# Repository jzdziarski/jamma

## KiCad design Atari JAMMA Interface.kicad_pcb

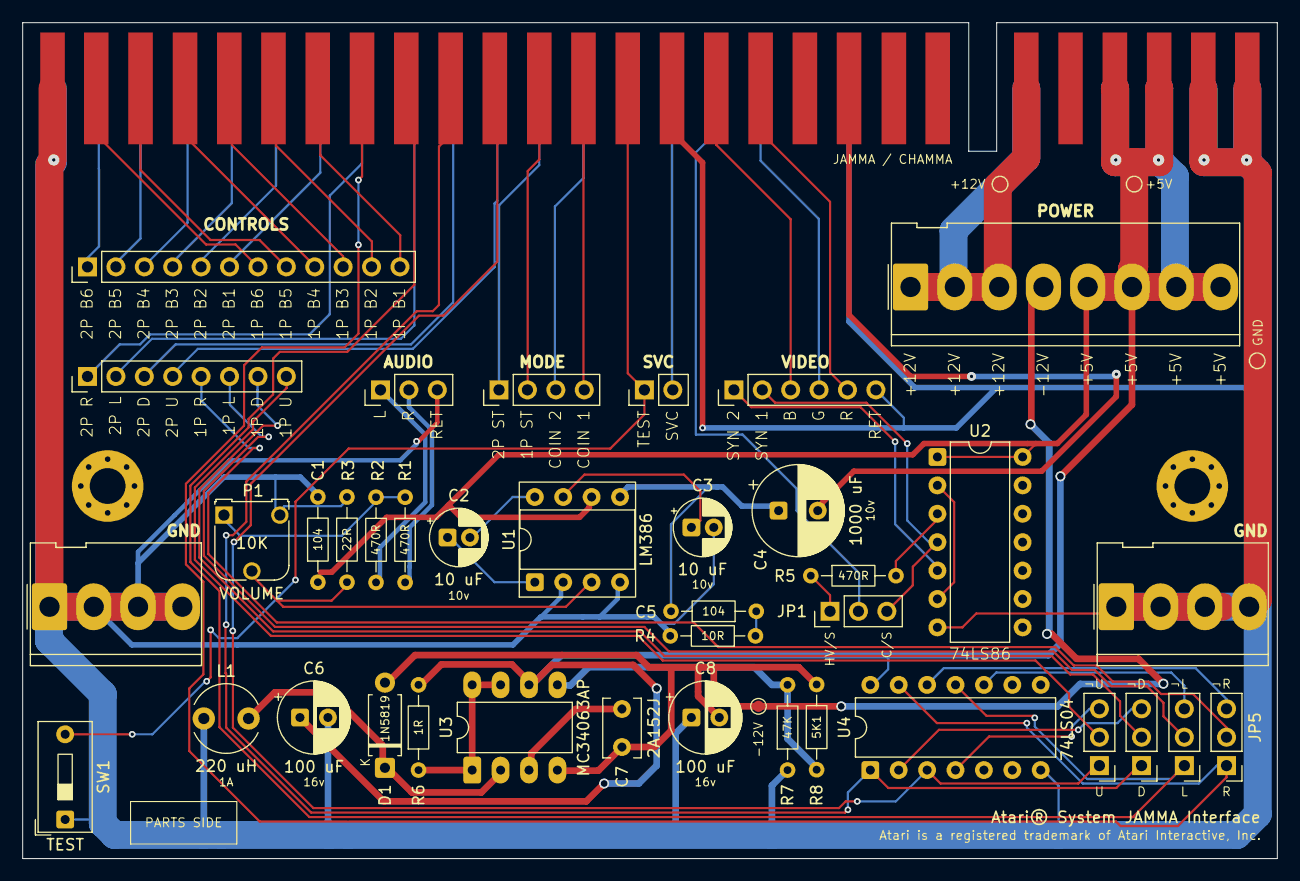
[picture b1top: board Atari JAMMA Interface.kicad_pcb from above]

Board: 2 copper layers, 112.2 x 74.8 mm, 43 parts (0 on the bottom side), 61 nets.

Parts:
+5V, +12V: TestPoint_Pad_D1.0mm
-12V: TestPoint_Pad_D1.0mm
AUDIO: PinHeader_1x03_P2.54mm_Vertical
C1, C5: 104; R_Axial_DIN0204_L3.6mm_D1.6mm_P7.62mm_Horizontal
C2, C3: 10 uF; CP_Radial_D5.0mm_P2.00mm
C4: 1000 uF; CP_Radial_D8.0mm_P3.50mm
C6, C8: 100 uF; CP_Radial_D6.3mm_P2.50mm
C7: 2A152J; C_Disc_D5.1mm_W3.2mm_P3.4mm
CONTROLS: PinHeader_1x12_P2.54mm_Vertical
D1: 1N5819; D_A-405_P7.62mm_Horizontal
DIRECTIONALS: PinHeader_1x08_P2.54mm_Vertical
GND: TestPoint_Pad_D1.0mm
GND#2, GND#3: Molex_KK-396_5273-04A_1x04_P3.96mm_Vertical
HV/S: PinHeader_1x03_P2.54mm_Vertical
HV/S#2, HV/S#3, HV/S#4, HV/S#5: PinHeader_1x03_P2.54mm_Vertical
JAMMA / CHAMMA: HDR_JAMMA_56P_EDGE_CONNECTOR
L1: 220 uH; L_Radial_D6.0mm_P4.00mm
MODE: PinHeader_1x04_P2.54mm_Vertical
P1: 10K; Potentiometer_Runtron_RM-065_Vertical
POWER: Molex_KK-396_5273-08A_1x08_P3.96mm_Vertical
R1, R2, R5: 470R; R_Axial_DIN0204_L3.6mm_D1.6mm_P7.62mm_Horizontal
R3: 22R; R_Axial_DIN0204_L3.6mm_D1.6mm_P7.62mm_Horizontal
R4: 10R; R_Axial_DIN0204_L3.6mm_D1.6mm_P7.62mm_Horizontal
R6: 1R; R_Axial_DIN0204_L3.6mm_D1.6mm_P7.62mm_Horizontal
R7: 47K; R_Axial_DIN0204_L3.6mm_D1.6mm_P7.62mm_Horizontal
R8: 5K1; R_Axial_DIN0204_L3.6mm_D1.6mm_P7.62mm_Horizontal
SVC: PinHeader_1x02_P2.54mm_Vertical
TEST: SW1; SW_DIP_SPSTx01_Slide_9.78x4.72mm_W7.62mm_P2.54mm
U1: LM386; DIP-8_W7.62mm_Socket
U2: DIP-14_W7.62mm
U3: MC34063AP; DIP-8_W7.62mm_LongPads
U4: 74LS04; DIP-14_W7.62mm
VIDEO: PinHeader_1x06_P2.54mm_Vertical

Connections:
1P_!D: HV/S#5.3, U4.2
1P_!L: HV/S.3, U4.10
1P_!R: HV/S#2.3, U4.12
1P_!U: HV/S#3.3, U4.4
1P_B1: CONTROLS.12, JAMMA / CHAMMA.22
1P_B2: CONTROLS.11, JAMMA / CHAMMA.23
1P_B3: CONTROLS.10, JAMMA / CHAMMA.24
1P_B4: CONTROLS.9, JAMMA / CHAMMA.25
1P_B5: CONTROLS.8, JAMMA / CHAMMA.26
1P_B6: CONTROLS.7, JAMMA / CHAMMA.27
1P_D: HV/S#5.1, JAMMA / CHAMMA.19, U4.1
1P_D_OUT: DIRECTIONALS.7, HV/S#5.2
1P_L: HV/S.1, JAMMA / CHAMMA.20, U4.11
1P_L_OUT: DIRECTIONALS.6, HV/S.2
1P_R: HV/S#2.1, JAMMA / CHAMMA.21, U4.13
1P_R_OUT: DIRECTIONALS.5, HV/S#2.2
1P_START: JAMMA / CHAMMA.17, MODE.2
1P_U: HV/S#3.1, JAMMA / CHAMMA.18, U4.3
1P_U_OUT: DIRECTIONALS.8, HV/S#3.2
2P_B1: CONTROLS.6, JAMMA / CHAMMA.Z
2P_B2: CONTROLS.5, JAMMA / CHAMMA.a
2P_B3: CONTROLS.4, JAMMA / CHAMMA.b
2P_B4: CONTROLS.3, JAMMA / CHAMMA.c
2P_B5: CONTROLS.2, JAMMA / CHAMMA.d
2P_B6: CONTROLS.1, JAMMA / CHAMMA.e
2P_D: DIRECTIONALS.3, JAMMA / CHAMMA.W
2P_L: DIRECTIONALS.2, JAMMA / CHAMMA.X
2P_R: DIRECTIONALS.1, JAMMA / CHAMMA.Y
2P_START: JAMMA / CHAMMA.U, MODE.1
2P_U: DIRECTIONALS.4, JAMMA / CHAMMA.V
+5V: +5V.1, C1.1, C6.1, JAMMA / CHAMMA.3, JAMMA / CHAMMA.4, JAMMA / CHAMMA.C, JAMMA / CHAMMA.D, POWER.5, POWER.6, POWER.7, POWER.8, R6.2, U1.6, U2.1, U2.14, U3.6, U4.14
+12V: +12V.1, JAMMA / CHAMMA.6, JAMMA / CHAMMA.F, POWER.1, POWER.2, POWER.3
-12V: -12V.1, C7.1, C8.2, D1.2, POWER.4, R8.2, U3.4
AUDIO_L: AUDIO.1, R2.2
AUDIO_MONO: P1.1, R1.1, R2.1
AUDIO_R: AUDIO.2, R1.2
C5_R4: C5.1, R4.1
CINV_R10_R9: R7.2, R8.1, U3.5
COIN_1: JAMMA / CHAMMA.16, MODE.4
COIN_2: JAMMA / CHAMMA.T, MODE.3
GND: AUDIO.3, C1.2, C3.2, C6.2, C8.1, GND.1, GND#2.1, GND#2.2, GND#2.3, GND#2.4, GND#3.1, GND#3.2, GND#3.3, GND#3.4, JAMMA / CHAMMA.1, JAMMA / CHAMMA.2, JAMMA / CHAMMA.14, JAMMA / CHAMMA.28, JAMMA / CHAMMA.A, JAMMA / CHAMMA.B, JAMMA / CHAMMA.L, JAMMA / CHAMMA.f, L1.1, P1.3, R3.2, R4.2, R7.1, TEST.1, U1.2, U1.4, U2.7, U4.7, VIDEO.6
PREAMP: P1.2, R3.1, U1.3
PREAMP_OUT: C4.1, C5.2, U1.5
R8: R6.1, U3.1, U3.7, U3.8
SERVICE: JAMMA / CHAMMA.R, SVC.2
SPKR+: C4.2, JAMMA / CHAMMA.10
SWE: D1.1, L1.2, U3.2
TEST: JAMMA / CHAMMA.15, SVC.1, TEST.2
U3_CAP: C7.2, U3.3
U4_BYPASS: C3.1, U1.7
U4_GAIN_P1: C2.1, U1.1
U4_GAIN_P8: C2.2, U1.8
VID_B: JAMMA / CHAMMA.13, VIDEO.3
VID_CSYNC: HV/S#4.2, JAMMA / CHAMMA.P
VID_G: JAMMA / CHAMMA.N, VIDEO.4
VID_NXOR: HV/S#4.1, R5.1
VID_NXOR_R5: R5.2, U2.3
VID_R: JAMMA / CHAMMA.12, VIDEO.5
VID_SYN1: HV/S#4.3, U2.4, VIDEO.2
VID_SYN2: U2.5, VIDEO.1
VID_XOR: U2.2, U2.6

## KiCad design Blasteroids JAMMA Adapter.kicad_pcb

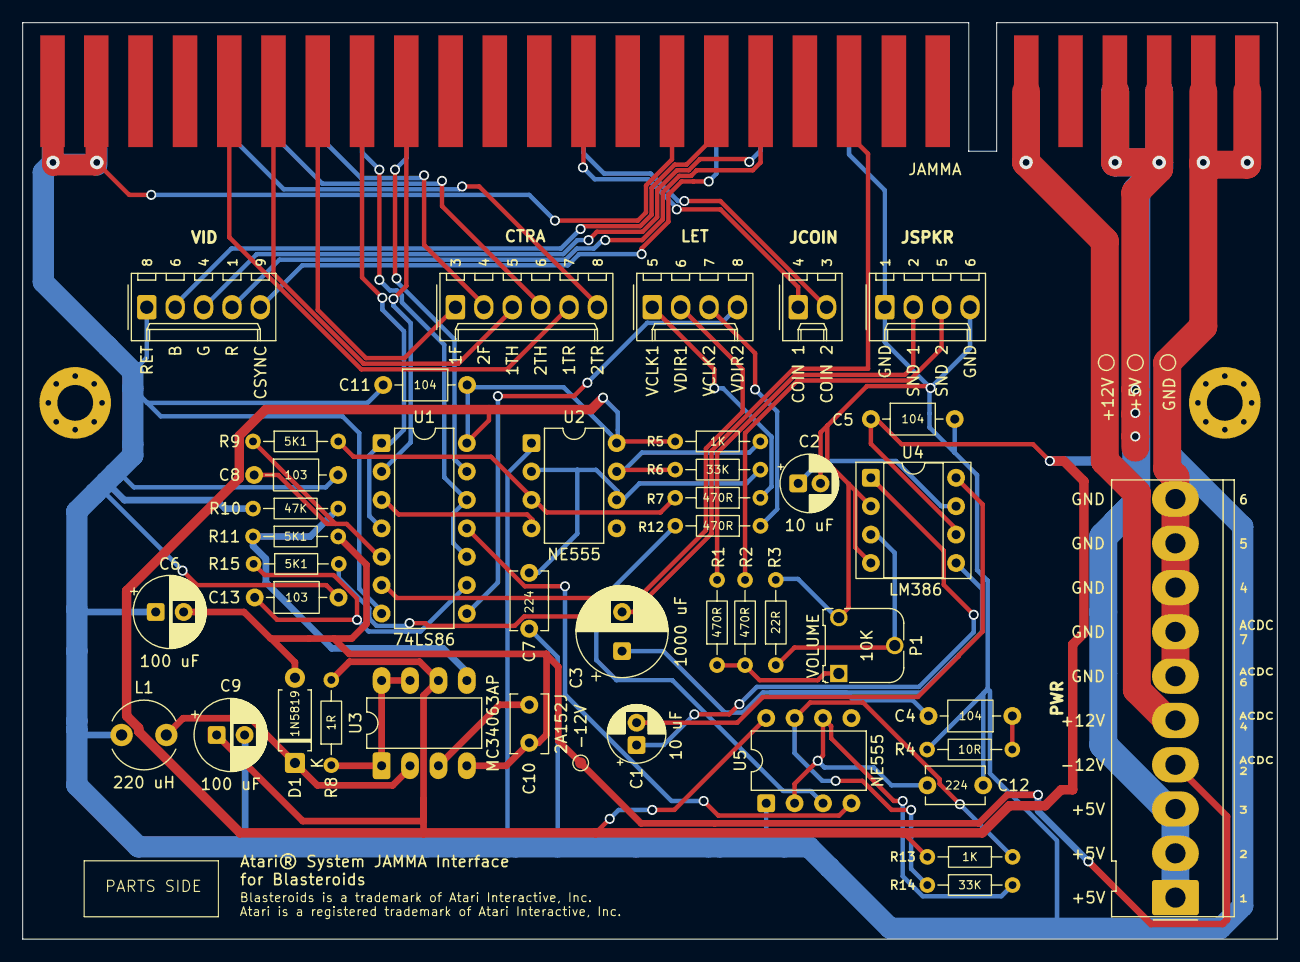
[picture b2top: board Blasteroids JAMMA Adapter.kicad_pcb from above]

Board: 2 copper layers, 112.2 x 82.0 mm, 49 parts (0 on the bottom side), 48 nets.

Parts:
+5V: TP2; TestPoint_Pad_D1.0mm
+12V: TP3; TestPoint_Pad_D1.0mm
-12V: TP4; TestPoint_Pad_D1.0mm
C1, C2: 10 uF; CP_Radial_D5.0mm_P2.00mm
C3: 1000 uF; CP_Radial_D8.0mm_P3.50mm
C4, C5, C11: 104; C_Axial_L3.8mm_D2.6mm_P7.50mm_Horizontal
C6, C9: 100 uF; CP_Radial_D6.3mm_P2.50mm
C7, C12: 224; C_Disc_D5.1mm_W3.2mm_P5.00mm
C8, C13: 103; C_Axial_L3.8mm_D2.6mm_P7.50mm_Horizontal
C10: 2A152J; C_Disc_D5.1mm_W3.2mm_P3.4mm
CTRA: Molex_KK-254_AE-6410-06A_1x06_P2.54mm_Vertical
D1: 1N5819; D_A-405_P7.62mm_Horizontal
GND: TP1; TestPoint_Pad_D1.0mm
JAMMA: HDR_JAMMA_56P_EDGE_CONNECTOR
JCOIN: Molex_KK-254_AE-6410-02A_1x02_P2.54mm_Vertical
JSPKR: Molex_KK-254_AE-6410-04A_1x04_P2.54mm_Vertical
L1: 220 uH; L_Radial_D6.0mm_P4.00mm
LET: Molex_KK-254_AE-6410-04A_1x04_P2.54mm_Vertical
P1: 10K; Potentiometer_Runtron_RM-065_Vertical
PMH1, PMH4: MountingHole_3.2mm_M3_Pad_Via
PWR: Molex_KK-396_5273-10A_1x10_P3.96mm_Vertical
R1: R1; R_Axial_DIN0204_L3.6mm_D1.6mm_P7.62mm_Horizontal
R2, R7, R12: 470R; R_Axial_DIN0204_L3.6mm_D1.6mm_P7.62mm_Horizontal
R3: 22R; R_Axial_DIN0204_L3.6mm_D1.6mm_P7.62mm_Horizontal
R4: R_Axial_DIN0204_L3.6mm_D1.6mm_P7.62mm_Horizontal
R5, R13: 1K; R_Axial_DIN0204_L3.6mm_D1.6mm_P7.62mm_Horizontal
R6, R14: 33K; R_Axial_DIN0204_L3.6mm_D1.6mm_P7.62mm_Horizontal
R8: 1R; R_Axial_DIN0204_L3.6mm_D1.6mm_P7.62mm_Horizontal
R9, R11, R15: 5K1; R_Axial_DIN0204_L3.6mm_D1.6mm_P7.62mm_Horizontal
R10: 47K; R_Axial_DIN0204_L3.6mm_D1.6mm_P7.62mm_Horizontal
U1: 74LS86; DIP-14_W7.62mm
U2, U5: NE555; DIP-8_W7.62mm
U3: MC34063AP; DIP-8_W7.62mm_LongPads
U4: LM386; DIP-8_W7.62mm_Socket
VID: Molex_KK-254_AE-6410-05A_1x05_P2.54mm_Vertical

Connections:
1P_B1: CTRA.1, JAMMA.22
1P_B2: CTRA.3, JAMMA.23
1P_B3: CTRA.5, JAMMA.24
1P_L: JAMMA.20, U1.2
1P_R: JAMMA.21, U1.1, U1.4
2P_B1: CTRA.2, JAMMA.Z
2P_B2: CTRA.4, JAMMA.a
2P_B3: CTRA.6, JAMMA.b
2P_L: JAMMA.X, U1.13
2P_R: JAMMA.Y, U1.10, U1.12
+5V: +5V.1, C5.1, C9.1, C11.2, JAMMA.3, JAMMA.4, JAMMA.C, JAMMA.D, PWR.1, PWR.2, PWR.3, R5.1, R8.2, R13.1, U1.14, U2.8, U3.6, U4.6, U5.8
+12V: +12V.1, JAMMA.6, JAMMA.F, PWR.5
-12V: -12V.1, C6.2, C10.1, D1.2, PWR.4, R11.2, U3.4
AUDIO_L: JSPKR.3, R2.2
AUDIO_MONO: P1.1, R1.1, R2.1
AUDIO_OUT: C3.2, JAMMA.10
AUDIO_PREAMP: P1.2, R3.1, U4.3
AUDIO_PREAMP_OUT: C3.1, C4.2, U4.5
AUDIO_R: JSPKR.2, R1.2
C4_R4: C4.1, R4.1
CINV_R10_R9: R10.2, R11.1, U3.5
COIN_1: JAMMA.16, JCOIN.1
COIN_2: JAMMA.T, JCOIN.2
GND: C2.2, C5.2, C6.1, C7.1, C8.2, C9.2, C11.1, C12.1, C13.2, GND.1, JAMMA.1, JAMMA.2, JAMMA.14, JAMMA.27, JAMMA.28, JAMMA.A, JAMMA.B, JAMMA.L, JAMMA.e, JAMMA.f, JSPKR.1, JSPKR.4, L1.1, P1.3, PWR.6, PWR.7, PWR.8, PWR.9, PWR.10, R3.2, R4.2, R10.1, U1.7, U2.1, U4.2, U4.4, U5.1, VID.1
R8: R8.1, U3.1, U3.7, U3.8
SWE: D1.1, L1.2, U3.2
U2_DIS: R5.2, R6.1, U2.7
U2_RESET: U1.3, U2.4
U2_THR: C7.2, R6.2, U2.2, U2.6
U3_CAP: C10.2, U3.3
U4_BYPASS: C2.1, U4.7
U4_GAIN_P1: C1.1, U4.1
U4_GAIN_P8: C1.2, U4.8
U5_DIS: R13.2, R14.1, U5.7
U5_RESET: U1.11, U5.4
U5_THR: C12.2, R14.2, U5.2, U5.6
VCLK1: R7.2, R9.2, U2.3
VCLK1_DELAYED: C8.1, R9.1, U1.5
VCLK1_OUT: LET.1, R7.1
VCLK2: R12.2, R15.2, U5.3
VCLK2_DELAYED: C13.1, R15.1, U1.9
VCLK2_OUT: LET.3, R12.1
VDIR1_OUT: LET.2, U1.6
VDIR2_OUT: LET.4, U1.8
VIDEO_B: JAMMA.13, VID.2
VIDEO_G: JAMMA.N, VID.3
VIDEO_R: JAMMA.12, VID.4
VIDEO_SYNC: JAMMA.P, VID.5

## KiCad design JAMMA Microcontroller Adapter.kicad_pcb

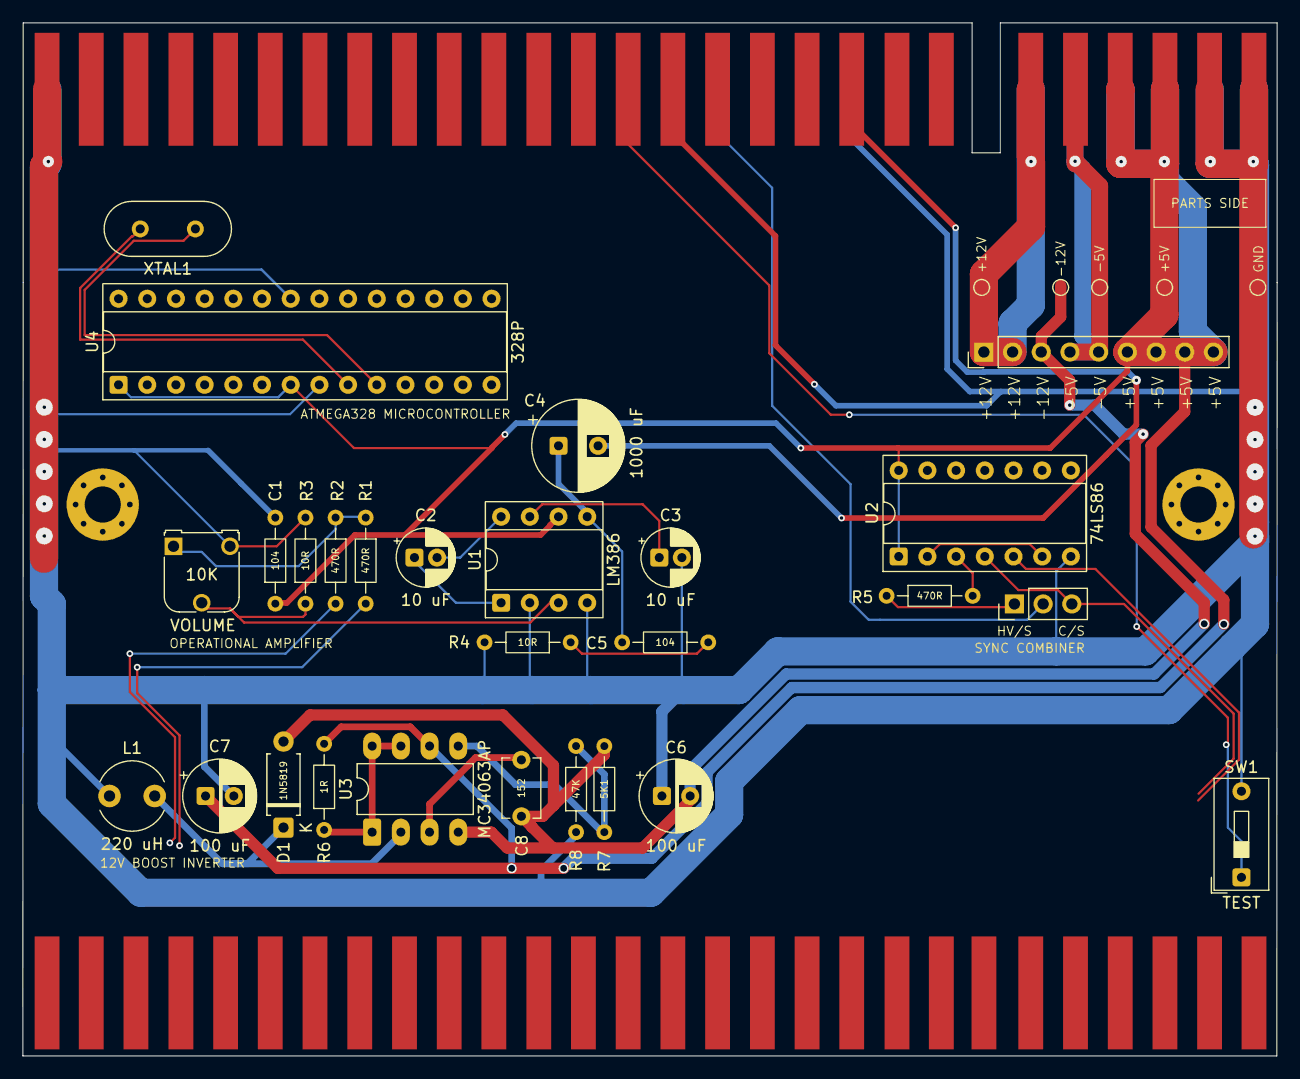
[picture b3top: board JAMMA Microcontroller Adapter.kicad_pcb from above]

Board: 2 copper layers, 111.0 x 91.4 mm, 34 parts (0 on the bottom side), 25 nets.

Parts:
+5V, +12V: TestPoint_Pad_D1.0mm
-5V, -12V: TestPoint_Pad_D1.0mm
C1, C5: 104; R_Axial_DIN0204_L3.6mm_D1.6mm_P7.62mm_Horizontal
C2, C3: 10 uF; CP_Radial_D5.0mm_P2.00mm
C4: 1000 uF; CP_Radial_D8.0mm_P3.50mm
C6, C7: 100 uF; CP_Radial_D6.3mm_P2.50mm
C8: 152; C_Disc_D5.1mm_W3.2mm_P5.00mm
D1: 1N5819; D_A-405_P7.62mm_Horizontal
GND: TestPoint_Pad_D1.0mm
HV/S: PinHeader_1x03_P2.54mm_Vertical
JAMMA: HDR_JAMMA_56P_EDGE_CONNECTOR; HDR_56P_EDGE_CONNECTOR
JAMMA#2: HDR_JAMMA_56P_EDGE_CONNECTOR
L1: 220 uH; L_Radial_D6.0mm_P4.00mm
POWER: PinHeader_1x09_P2.54mm_Vertical
R1, R2, R5: 470R; R_Axial_DIN0204_L3.6mm_D1.6mm_P7.62mm_Horizontal
R3, R4: 10R; R_Axial_DIN0204_L3.6mm_D1.6mm_P7.62mm_Horizontal
R6: 1R; R_Axial_DIN0204_L3.6mm_D1.6mm_P7.62mm_Horizontal
R7: 5K1; R_Axial_DIN0204_L3.6mm_D1.6mm_P7.62mm_Horizontal
R8: 47K; R_Axial_DIN0204_L3.6mm_D1.6mm_P7.62mm_Horizontal
TEST: SW1; SW_DIP_SPSTx01_Slide_9.78x4.72mm_W7.62mm_P2.54mm
U1: LM386; DIP-8_W7.62mm_Socket
U2: 74LS86; DIP-14_W7.62mm_Socket
U3: MC34063AP; DIP-8_W7.62mm_LongPads
U4: 328P; DIP-28_W7.62mm_Socket
VOLUME: 10K; Potentiometer_Runtron_RM-065_Vertical
XTAL1: Crystal_HC49-4H_Vertical

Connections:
+5V: +5V.1, C1.1, C7.1, JAMMA#2.3, JAMMA#2.4, JAMMA#2.C, JAMMA#2.D, POWER.6, POWER.7, POWER.8, POWER.9, R6.2, U1.6, U2.1, U2.14, U3.6, U4.1, U4.7
+12V: +12V.1, JAMMA#2.6, JAMMA#2.F, POWER.1, POWER.2
-5V: -5V.1, JAMMA#2.5, JAMMA#2.E, POWER.4, POWER.5
-12V: -12V.1, C6.2, C8.1, D1.2, POWER.3, R7.2, U3.4
AUDIO_MONO: R1.1, R2.1, VOLUME.1
C5_R4: C5.1, R4.1
CINV_R7_R8: R7.1, R8.2, U3.5
GND: C1.2, C3.2, C6.1, C7.2, GND.1, JAMMA#2.1, JAMMA#2.2, JAMMA#2.14, JAMMA#2.28, JAMMA#2.A, JAMMA#2.B, JAMMA#2.L, JAMMA#2.f, L1.1, R3.2, R4.2, R8.1, TEST.2, U1.2, U1.4, U2.7, U4.8, U4.22, VOLUME.3
PB6: U4.9, XTAL1.2
PB7: U4.10, XTAL1.1
PREAMP: R3.1, U1.3, VOLUME.2
PREAMP_OUT: C4.1, C5.2, U1.5
R6: R6.1, U3.1, U3.7, U3.8
SPKR+: C4.2, JAMMA#2.10
SWE: D1.1, L1.2, U3.2
TEST: JAMMA#2.15, TEST.1
U3_CAP: C8.2, U3.3
U4_BYPASS: C3.1, U1.7
U4_GAIN_P1: C2.1, U1.1
U4_GAIN_P8: C2.2, U1.8
VID_CSYNC: HV/S.2, JAMMA#2.P
VID_NXOR: HV/S.1, R5.1
VID_NXOR_R5: R5.2, U2.3
VID_SYN1: HV/S.3, U2.4
VID_XOR: U2.2, U2.6

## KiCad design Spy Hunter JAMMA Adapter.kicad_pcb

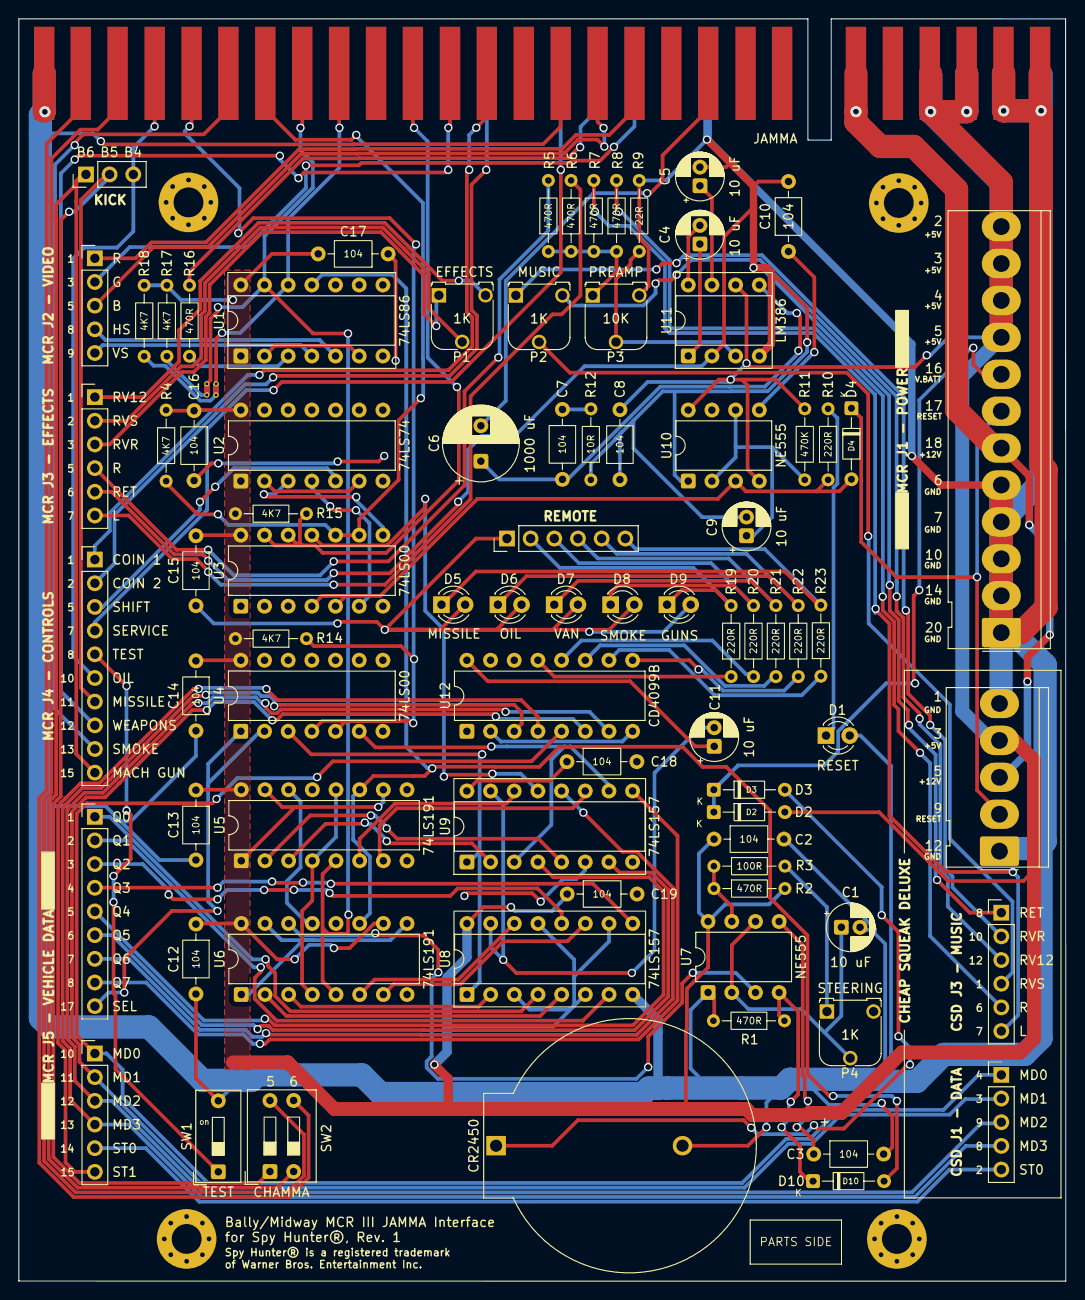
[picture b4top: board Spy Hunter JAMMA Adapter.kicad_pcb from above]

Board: 2 copper layers, 112.3 x 135.4 mm, 86 parts (0 on the bottom side), 101 nets.

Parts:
C1, C4, C5, C9, C11: 10 uF; CP_Radial_D5.0mm_P2.00mm
C2, C3, C7, C8, C10, C12, C13, C14, C15, C16, C17, C18, C19: 104; C_Axial_L3.8mm_D2.6mm_P7.50mm_Horizontal
C6: 1000 uF; CP_Radial_D8.0mm_P3.80mm
CR2450: BatteryHolder_ComfortableElectronic_CH273-2450_1x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; BatteryHolder_ComfortableElectronic_CH273-2450_1x2450
CSDJ1: PinHeader_1x05_P2.54mm_Vertical
CSDJ2: Molex_KK-396_5273-05A_1x05_P3.96mm_Vertical
CSDJ3: PinHeader_1x06_P2.54mm_Vertical
D1, D5, D6, D7, D8, D9: LED; LED_D3.0mm
D2, D3: 1N5817; D_DO-34_SOD68_P7.62mm_Horizontal
D4, D10: 1N4148; D_DO-34_SOD68_P7.62mm_Horizontal
JAMMA: HDR_JAMMA_56P_EDGE_CONNECTOR
KICK: PinHeader_1x03_P2.54mm_Vertical
MCR J5 - LAMPS: PinHeader_1x06_P2.54mm_Vertical
MCRJ1: Molex_KK-396_5273-12A_1x12_P3.96mm_Vertical
MCRJ2: PinHeader_1x05_P2.54mm_Vertical
MCRJ3: PinHeader_1x06_P2.54mm_Vertical
MCRJ4: PinHeader_1x10_P2.54mm_Vertical
MCRJ5: PinHeader_1x09_P2.54mm_Vertical
P1, P2, P4: 1K; Potentiometer_Runtron_RM-065_Vertical
P3: 10K; Potentiometer_Runtron_RM-065_Vertical
PMH1, PMH2, PMH3, PMH4: MountingHole_3.2mm_M3_Pad_Via
R1, R2, R5, R6, R7, R8, R16: 470R; R_Axial_DIN0204_L3.6mm_D1.6mm_P7.62mm_Horizontal
R3: 100R; R_Axial_DIN0204_L3.6mm_D1.6mm_P7.62mm_Horizontal
R4, R14, R15, R17, R18: 4K7; R_Axial_DIN0204_L3.6mm_D1.6mm_P7.62mm_Horizontal
R9: 22R; R_Axial_DIN0204_L3.6mm_D1.6mm_P7.62mm_Horizontal
R10, R19, R20, R21, R22, R23: 220R; R_Axial_DIN0204_L3.6mm_D1.6mm_P7.62mm_Horizontal
R11: 470K; R_Axial_DIN0204_L3.6mm_D1.6mm_P7.62mm_Horizontal
R12: R_Axial_DIN0204_L3.6mm_D1.6mm_P7.62mm_Horizontal
REMOTE: PinHeader_1x06_P2.54mm_Vertical
SW2: SW_DIP_SPSTx02_Slide_9.78x7.26mm_W7.62mm_P2.54mm
TEST: SW1; SW_DIP_SPSTx01_Slide_9.78x4.72mm_W7.62mm_P2.54mm
U1: 74LS86; DIP-14_W7.62mm_Socket
U2: 74LS74; DIP-14_W7.62mm
U3, U4: 74LS00; DIP-14_W7.62mm
U5, U6: 74LS191; DIP-16_W7.62mm
U7, U10: NE555; DIP-8_W7.62mm
U8, U9: 74LS157; DIP-16_W7.62mm_Socket
U11: LM386; DIP-8_W7.62mm_Socket
U12: CD4099B; DIP-16_W7.62mm

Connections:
1P_B1: JAMMA.22, R4.1, U3.9, U3.10
1P_B2: JAMMA.23, MCRJ4.9
1P_B3: JAMMA.24, R14.1, U4.4, U4.5
1P_B4: JAMMA.25, KICK.3, MCRJ4.6
1P_B5: KICK.2, MCRJ4.7, SW2.1
1P_B5_CHAMMA: JAMMA.26, SW2.4
1P_B6: KICK.1, MCRJ4.10, SW2.2
1P_B6_CHAMMA: JAMMA.27, SW2.3
1P_GAS: U4.6, U9.3, U9.10
1P_LEFT: JAMMA.20, U1.12
1P_RIGHT: JAMMA.21, U1.13, U5.5, U6.5
1P_START: JAMMA.17, MCRJ4.8
1P_TURBO: U3.11, U9.13
1P_U: JAMMA.18, R15.1, U3.12, U3.13
!RST: U2.4, U3.6
!SEL: U4.3, U8.1, U9.1
!SHIFT_LATCH: U2.2, U2.6
+5V: C2.1, C8.2, C11.1, C12.1, C13.1, C14.1, C15.1, C16.1, C17.2, C18.1, C19.1, CSDJ2.4, D2.2, JAMMA.3, JAMMA.4, JAMMA.C, JAMMA.D, MCRJ1.9, MCRJ1.10, MCRJ1.11, MCRJ1.12, R2.2, R4.2, R11.2, R14.2, R15.2, R17.2, R18.2, U1.1, U1.14, U2.1, U2.14, U3.14, U4.14, U5.1, U5.10, U5.15, U5.16, U6.10, U6.16, U7.8, U8.3, U8.6, U8.10, U8.13, U8.16, U9.6, U9.16, U10.4, U10.8, U11.6, U12.16
+5V_RST: CSDJ2.2, D4.1, MCRJ1.7
+12V: CSDJ2.3, JAMMA.6, JAMMA.F, MCRJ1.6
AUDIO_MONO: P3.1, R5.1, R6.1, R7.1, R8.1
AUDIO_OUT: C6.2, JAMMA.10
AUDIO_PREAMP: P3.2, R9.1, U11.3
AUDIO_PREAMP_OUT: C6.1, C7.2, U11.5
BATT+: CR2450.1, D3.2
C7_R12: C7.1, R12.1
CLK: U6.14, U7.3
CLK_GATE: D10.2, U1.11, U5.11, U6.11
COIN_1: JAMMA.16, MCRJ4.1
COIN_2: JAMMA.T, MCRJ4.2
D5: D5.1, R23.2, REMOTE.6
D6: D6.1, R22.2, REMOTE.5
D7: D7.1, R21.2, REMOTE.4
D8: D8.1, R20.2, REMOTE.3
D9: D9.1, R19.2, REMOTE.2
EFFECTS_L: MCRJ3.6, R6.2
EFFECTS_R: MCRJ3.4, R5.2
EFFECTS_RV12: MCRJ3.1, P1.3
EFFECTS_RVR: MCRJ3.3, P1.1
EFFECTS_RVS: MCRJ3.2, P1.2
GND: C1.2, C2.2, C3.2, C5.2, C8.1, C9.2, C10.2, C11.2, C12.2, C13.2, C14.2, C15.2, C16.2, C17.1, C18.2, C19.2, CR2450.2, CSDJ2.1, CSDJ2.5, CSDJ3.1, D1.2, D5.2, D6.2, D7.2, D8.2, D9.2, JAMMA.1, JAMMA.2, JAMMA.14, JAMMA.28, JAMMA.A, JAMMA.B, JAMMA.L, JAMMA.f, MCRJ1.1, MCRJ1.2, MCRJ1.3, MCRJ1.4, MCRJ1.5, MCRJ3.5, P3.3, R1.2, R9.2, R12.2, REMOTE.1, TEST.2, U1.7, U2.7, U3.7, U4.7, U5.8, U5.9, U6.1, U6.8, U6.9, U6.15, U7.1, U8.8, U8.15, U9.8, U9.15, U10.1, U11.2, U11.4, U12.2, U12.8
J5_ST0: CSDJ1.5, MCR J5 - LAMPS.5
MAXMIN_CTEN: U5.4, U5.12, U6.4
MUSIC_L: CSDJ3.6, R7.2
MUSIC_R: CSDJ3.5, R8.2
MUSIC_RV12: CSDJ3.3, P2.3
MUSIC_RVR: CSDJ3.2, P2.1
MUSIC_RVS: CSDJ3.4, P2.2
Q0: MCRJ5.1, U8.4
Q1: MCRJ5.2, U8.7
Q2: MCRJ5.3, U8.12
Q3: MCRJ5.4, U8.9
Q4: MCRJ5.5, U9.4
Q5: MCRJ5.6, U9.7
Q6: MCRJ5.7, U9.12
Q7: MCRJ5.8, U9.9
RST: D4.2, R10.1, U3.4, U3.5, U10.3
RST_LED: D1.1, R10.2
SEL: MCRJ5.9, U4.1, U4.2
SERVICE_SW: JAMMA.R, MCRJ4.4
SHIFT_LATCH: MCRJ4.3, U2.5
TEST_SW: MCRJ4.5, TEST.1
U2_CLK: U2.3, U3.8
U6_RCO: U5.14, U6.13
U7_CTL: C3.1, U7.5
U7_DIS: R2.1, R3.1, U7.7
U7_DIS_P4_1: P4.1, R3.2
U7_RESET: D10.1, R1.1, U7.4
U7_TRIG: C1.1, P4.2, U7.2, U7.6
U8_I0a: U6.3, U8.2
U8_I0b: U6.2, U8.5
U8_I0c: U6.6, U8.14
U8_I0d: U6.7, U8.11
U9_I0a: U5.3, U9.2
U9_I0b: U5.2, U9.5
U9_I0c: U5.6, U9.14
U9_I0d: U5.7, U9.11
U10_CTL: C10.1, U10.5
U10_TRIG: C9.1, R11.1, U10.2, U10.6
U11_BYPASS: C5.1, U11.7
U11_GAIN_P1: C4.1, U11.1
U11_GAIN_P8: C4.2, U11.8
U12_A0: CSDJ1.1, MCR J5 - LAMPS.1, U12.5
U12_A1: CSDJ1.2, MCR J5 - LAMPS.2, U12.6
U12_A2: CSDJ1.3, MCR J5 - LAMPS.3, U12.7
U12_DATA: CSDJ1.4, MCR J5 - LAMPS.4, U12.3
U12_DISABLE: MCR J5 - LAMPS.6, U12.4
U12_Q0: R22.1, U12.9
U12_Q1: R23.1, U12.10
U12_Q2: R21.1, U12.11
U12_Q3: R20.1, U12.12
U12_Q4: R19.1, U12.13
V.BATT: D2.1, D3.1, MCRJ1.8
VIDEO_B: JAMMA.13, MCRJ2.3
VIDEO_G: JAMMA.N, MCRJ2.2
VIDEO_HSYNC: MCRJ2.4, U1.5
VIDEO_NXOR: R16.1, U1.3
VIDEO_R: JAMMA.12, MCRJ2.1
VIDEO_SYNC_OUT: JAMMA.P, R16.2
VIDEO_VSYNC: MCRJ2.5, U1.4
VIDEO_XOR: U1.2, U1.6

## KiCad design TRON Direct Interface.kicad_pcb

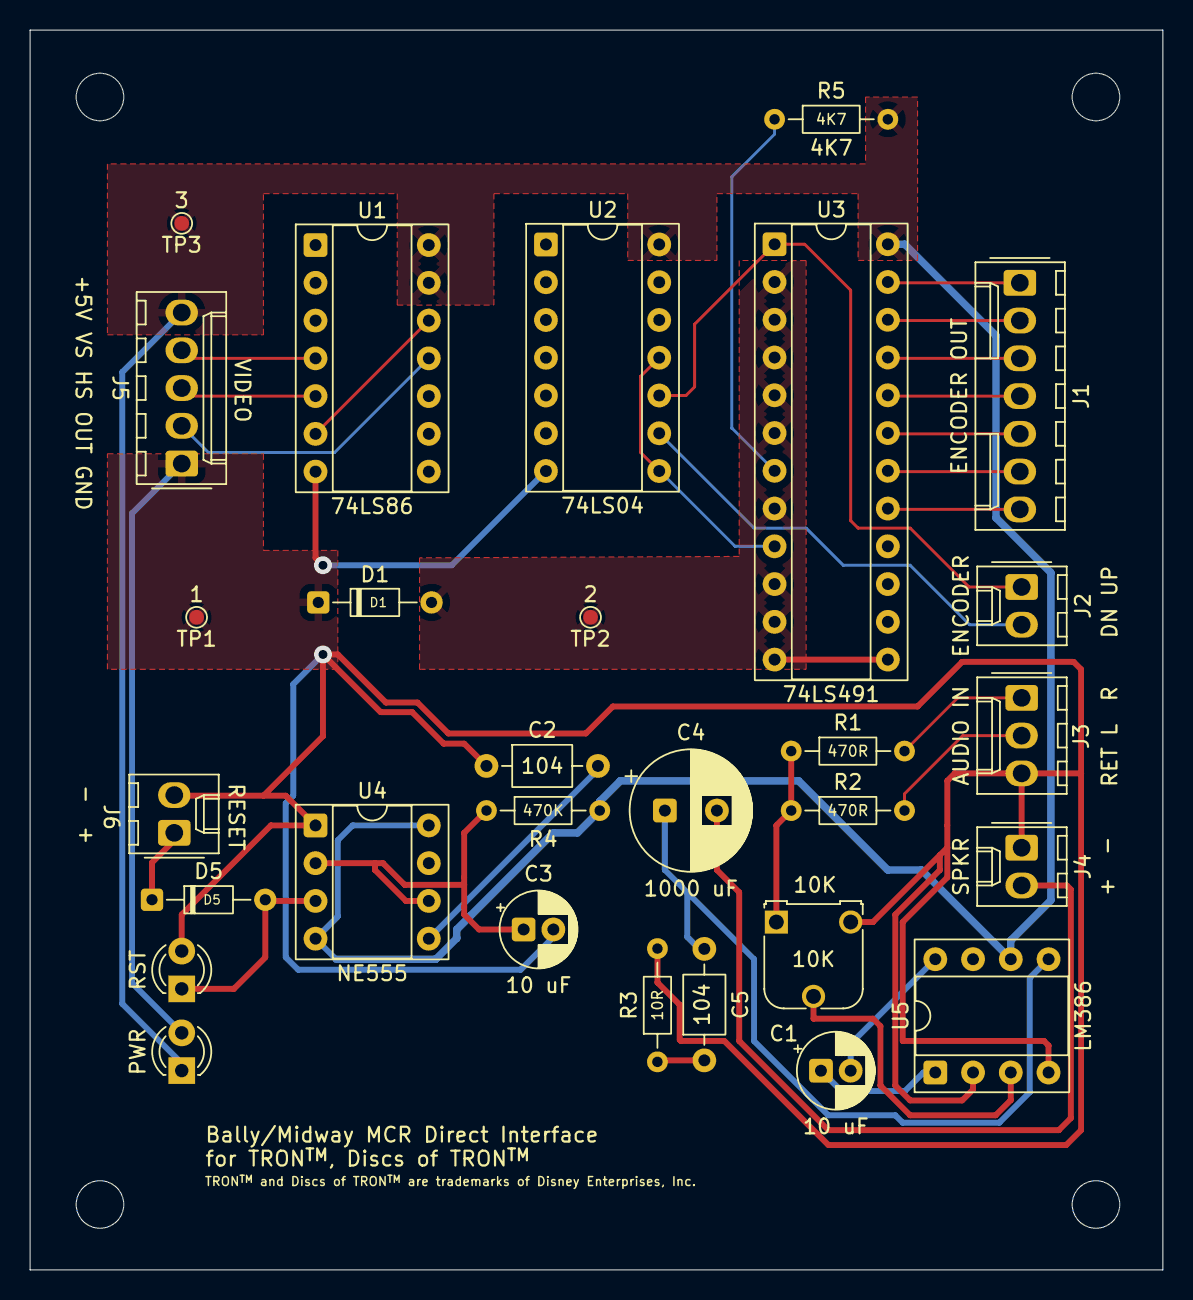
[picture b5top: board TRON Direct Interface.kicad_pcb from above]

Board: 2 copper layers, 76.2 x 83.4 mm, 33 parts (0 on the bottom side), 31 nets.

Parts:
10K: 3362; Potentiometer_Runtron_RM-065_Vertical
104: C5; C_Axial_L3.8mm_D2.6mm_P7.50mm_Horizontal
 : MountingHole_3.2mm_M3
 #2: MountingHole_3.2mm_M3
C1, C3: 10 uF; CP_Radial_D5.0mm_P2.00mm
C2: 104; C_Axial_L3.8mm_D2.6mm_P7.50mm_Horizontal
C4: 1000 uF; CP_Radial_D8.0mm_P3.50mm
D1: 200ma; D_DO-34_SOD68_P7.62mm_Horizontal
D5: D_DO-34_SOD68_P7.62mm_Horizontal
J1: ENCODER OUT; Molex_KK-254_AE-6410-07A_1x07_P2.54mm_Vertical
J2: ENCODER; Molex_KK-254_AE-6410-02A_1x02_P2.54mm_Vertical
J3: AUDIO IN; Molex_KK-254_AE-6410-03A_1x03_P2.54mm_Vertical
J4: SPKR; Molex_KK-254_AE-6410-02A_1x02_P2.54mm_Vertical
J5: VIDEO; Molex_KK-254_AE-6410-05A_1x05_P2.54mm_Vertical
J6: RESET; Molex_KK-254_AE-6410-02A_1x02_P2.54mm_Vertical
M3, M3#2: M3; MountingHole_3.2mm_M3
PWR: LED; LED_D3.0mm
R1: R1; R_Axial_DIN0204_L3.6mm_D1.6mm_P7.62mm_Horizontal
R2: 470R; R_Axial_DIN0204_L3.6mm_D1.6mm_P7.62mm_Horizontal
R3: R_Axial_DIN0204_L3.6mm_D1.6mm_P7.62mm_Horizontal
R4: R4; R_Axial_DIN0204_L3.6mm_D1.6mm_P7.62mm_Horizontal
R5: 4K7; R_Axial_DIN0204_L3.6mm_D1.6mm_P7.62mm_Horizontal
RST: LED; LED_D3.0mm
TP1: 1; TestPoint_Pad_D1.0mm
TP2: 2; TestPoint_Pad_D1.0mm
TP3: 3; TestPoint_Pad_D1.0mm
U1: 74LS86; DIP-14_W7.62mm_Socket
U2: 74LS04; DIP-14_W7.62mm_Socket
U3: 74LS491; DIP-24_W7.62mm_Socket
U4: NE555; DIP-8_W7.62mm_Socket
U5: LM386; DIP-8_W7.62mm_Socket

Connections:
+5V: J5.5, PWR.1, R4.2, R5.2, TP3.1, U1.13, U1.14, U2.14, U3.24, U4.4, U4.8, U5.6
AUDIO_L: J3.2, R2.2
AUDIO_MONO: 10K.1, R1.1, R2.1
AUDIO_OUT: C4.2, J4.2
AUDIO_R: J3.1, R1.2
C5_R3: 104.1, R3.1
CLK: J2.1, U2.10, U3.1
D3: D1.2, TP2.1, U3.2, U3.3, U3.4, U3.5, U3.6, U3.8, U3.10, U3.11, U3.12, U3.13
DN: U2.8, U2.11, U3.9
DN_IN: J2.2, U2.9
E1: J1.1, U3.23
E2: J1.2, U3.22
E3: J1.3, U3.21
E4: J1.4, U3.20
E5: J1.5, U3.19
E6: J1.6, U3.18
E7: J1.7, U3.17
GND: 10K.3, C2.1, C3.2, D1.1, J3.3, J4.1, J5.1, J6.2, PWR.2, R3.2, RST.2, TP1.1, U1.7, U2.7, U4.1, U5.2, U5.4
LD: R5.1, U3.7
PREAMP_GAIN_P1: C1.1, U5.1
PREAMP_GAIN_P8: C1.2, U5.8
PREAMP_OUT: 104.2, C4.1, U5.5
PREAMP_POT_P2: 10K.2, U5.3
RESET_5V: D5.2, RST.1, U4.3
RESET_5V_OUT: D5.1, J6.1
U1_IC_P6_P12: U1.6, U1.12
U4_CONTROL: C2.2, U4.5
U4_TRIGGER: C3.1, R4.1, U4.2, U4.6
VIDEO_CSYNC: J5.2, U1.11
VIDEO_HSYNC: J5.3, U1.5
VIDEO_VSYNC: J5.4, U1.4

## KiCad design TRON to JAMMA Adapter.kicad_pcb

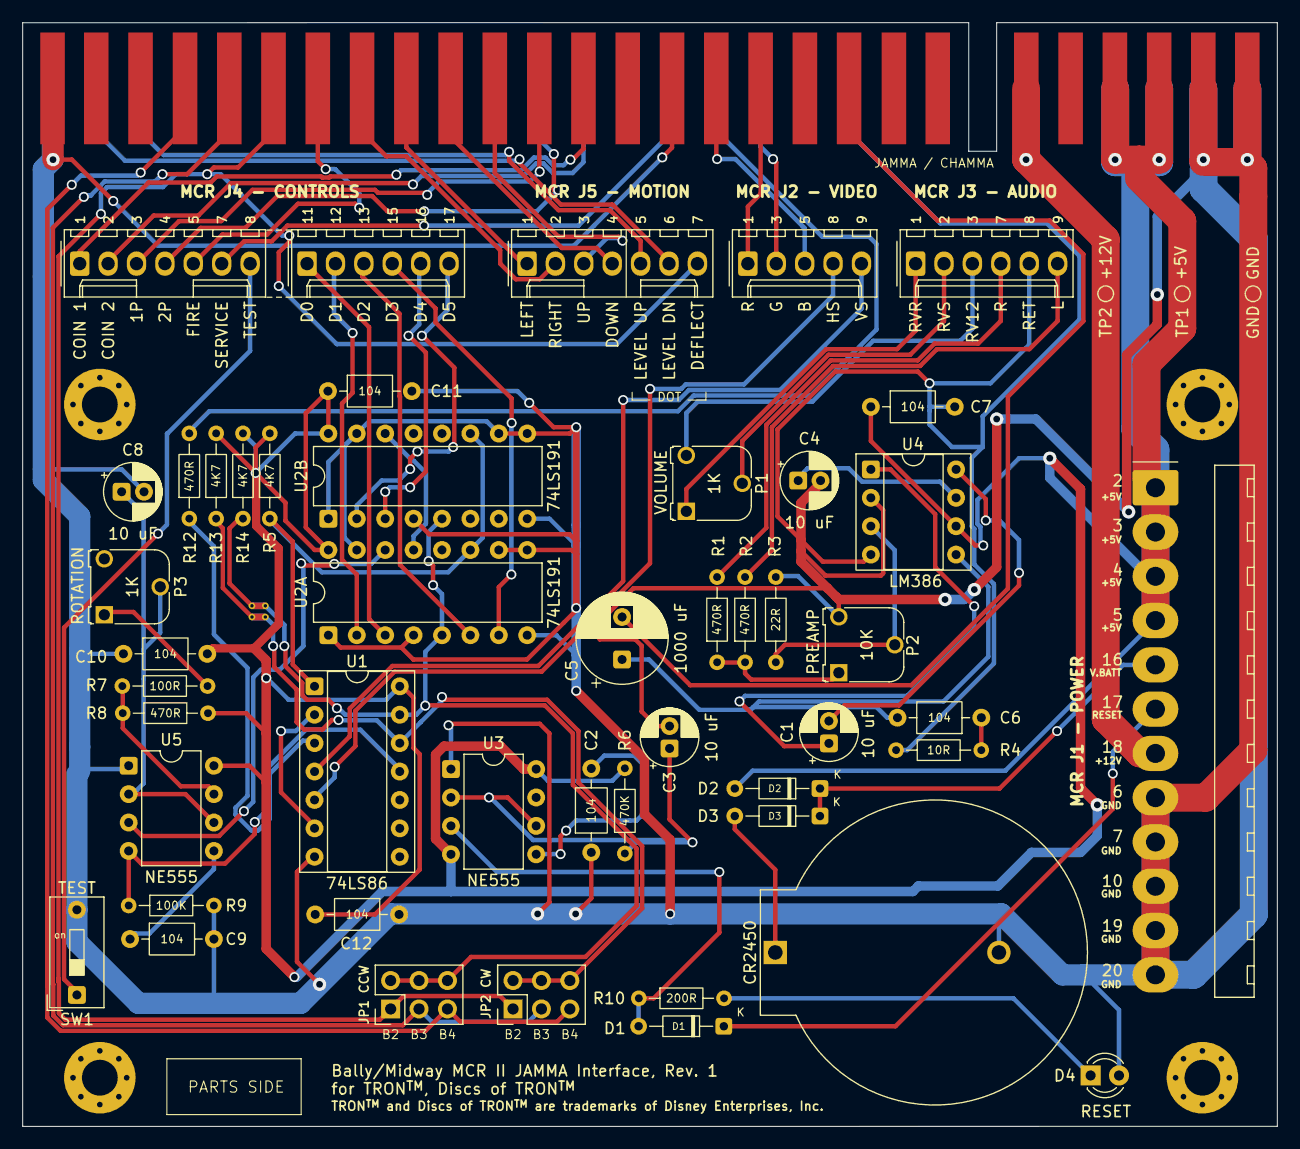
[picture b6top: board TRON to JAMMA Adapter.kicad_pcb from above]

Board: 2 copper layers, 112.2 x 98.7 mm, 56 parts (0 on the bottom side), 63 nets.

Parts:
+5V: TP1; TestPoint_Pad_D1.0mm
+12V: TP2; TestPoint_Pad_D1.0mm
C1, C3, C4, C8: 10 uF; CP_Radial_D5.0mm_P2.00mm
C2, C6, C7, C9, C10, C11, C12: 104; C_Axial_L3.8mm_D2.6mm_P7.50mm_Horizontal
C5: 1000 uF; CP_Radial_D8.0mm_P3.80mm
CR2450: BatteryHolder_ComfortableElectronic_CH273-2450_1x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; BatteryHolder_ComfortableElectronic_CH273-2450_1x2450
D1: 1N4148; D_DO-34_SOD68_P7.62mm_Horizontal
D2, D3: 1N5817; D_DO-34_SOD68_P7.62mm_Horizontal
D4: LED; LED_D3.0mm
GND: GND; TestPoint_Pad_D1.0mm
JAMMA / CHAMMA: HDR_JAMMA_56P_EDGE_CONNECTOR
JP1 CCW, JP2 CW: PinHeader_2x03_P2.54mm_Vertical
MCRJ1: Molex_KK-396_A-41792-0012_1x12_P3.96mm_Horizontal
MCRJ2: Molex_KK-254_AE-6410-05A_1x05_P2.54mm_Vertical
MCRJ3, MCRJ4B: Molex_KK-254_AE-6410-06A_1x06_P2.54mm_Vertical
MCRJ4A, MCRJ5: Molex_KK-254_AE-6410-07A_1x07_P2.54mm_Vertical
P1, P3: 1K; Potentiometer_Runtron_RM-065_Vertical
P2: 10K; Potentiometer_Runtron_RM-065_Vertical
PMH1, PMH2, PMH3, PMH4: MountingHole_3.2mm_M3_Pad_Via
R1: R1; R_Axial_DIN0204_L3.6mm_D1.6mm_P7.62mm_Horizontal
R2, R8, R12: 470R; R_Axial_DIN0204_L3.6mm_D1.6mm_P7.62mm_Horizontal
R3: 22R; R_Axial_DIN0204_L3.6mm_D1.6mm_P7.62mm_Horizontal
R4: R_Axial_DIN0204_L3.6mm_D1.6mm_P7.62mm_Horizontal
R5, R13, R14: 4K7; R_Axial_DIN0204_L3.6mm_D1.6mm_P7.62mm_Horizontal
R6: 470K; R_Axial_DIN0204_L3.6mm_D1.6mm_P7.62mm_Horizontal
R7: 100R; R_Axial_DIN0204_L3.6mm_D1.6mm_P7.62mm_Horizontal
R9: 100K; R_Axial_DIN0204_L3.6mm_D1.6mm_P7.62mm_Horizontal
R10: 200R; R_Axial_DIN0204_L3.6mm_D1.6mm_P7.62mm_Horizontal
TEST: SW1; SW_DIP_SPSTx01_Slide_9.78x4.72mm_W7.62mm_P2.54mm
U1: 74LS86; DIP-14_W7.62mm_Socket
U2A, U2B: 74LS191; DIP-16_W7.62mm
U3, U5: NE555; DIP-8_W7.62mm
U4: LM386; DIP-8_W7.62mm_Socket

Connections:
1P_B1: JAMMA / CHAMMA.22, MCRJ4A.5
1P_B2: JAMMA / CHAMMA.23, JP1 CCW.1, JP2 CW.1, MCRJ5.7
1P_B3: JAMMA / CHAMMA.24, JP1 CCW.3, JP2 CW.3
1P_B4: JAMMA / CHAMMA.25, JP1 CCW.5, JP2 CW.5
1P_B5: JAMMA / CHAMMA.d, MCRJ5.5
1P_B6: JAMMA / CHAMMA.e, MCRJ5.6
1P_D: JAMMA / CHAMMA.19, MCRJ5.4
1P_L: JAMMA / CHAMMA.20, MCRJ5.1
1P_R: JAMMA / CHAMMA.21, MCRJ5.2
1P_START: JAMMA / CHAMMA.17, MCRJ4A.3
1P_U: JAMMA / CHAMMA.18, MCRJ5.3
2P_START: JAMMA / CHAMMA.U, MCRJ4A.4
+5V: +5V.1, C7.1, C10.2, C11.1, C12.2, D2.2, JAMMA / CHAMMA.3, JAMMA / CHAMMA.4, JAMMA / CHAMMA.C, JAMMA / CHAMMA.D, MCRJ1.1, MCRJ1.2, MCRJ1.3, MCRJ1.4, R5.2, R6.2, R8.2, R13.2, R14.2, U1.14, U2A.16, U2B.16, U3.4, U3.8, U4.6, U5.8
+5V_R5: R5.1, U1.1, U2A.11, U2B.11
+12V_IN: +12V.1, JAMMA / CHAMMA.6, JAMMA / CHAMMA.F, MCRJ1.7
AUDIO_L: MCRJ3.6, R2.2
AUDIO_MONO: P2.1, R1.1, R2.1
AUDIO_OUT: C5.2, JAMMA / CHAMMA.10
AUDIO_PREAMP: P2.2, R3.1, U4.3
AUDIO_PREAMP_OUT: C5.1, C6.2, U4.5
AUDIO_R: MCRJ3.4, R1.2
BATTERY: CR2450.1, D3.2
C6_R4: C6.1, R4.1
CCW_IN: JP1 CCW.2, JP1 CCW.4, JP1 CCW.6, U1.13, U2A.5, U2B.5
CLK: U2A.14, U5.3
CLK_GATE: R9.1, U1.11, U5.4
COIN_1: JAMMA / CHAMMA.16, MCRJ4A.1
COIN_2: JAMMA / CHAMMA.T, MCRJ4A.2
CW_IN: JP2 CW.2, JP2 CW.4, JP2 CW.6, U1.12
E1: MCRJ4B.1, U2A.3
E2: MCRJ4B.2, U2A.2
E3: MCRJ4B.3, U2A.6
E4: MCRJ4B.4, U2A.7
E5: MCRJ4B.5, U2B.3
E6: MCRJ4B.6, U2B.2
GND: C2.1, C3.2, C4.2, C7.2, C8.2, C9.2, C10.1, C11.2, C12.1, CR2450.2, D4.2, GND.1, JAMMA / CHAMMA.1, JAMMA / CHAMMA.2, JAMMA / CHAMMA.14, JAMMA / CHAMMA.28, JAMMA / CHAMMA.A, JAMMA / CHAMMA.B, JAMMA / CHAMMA.L, JAMMA / CHAMMA.f, MCRJ1.8, MCRJ1.9, MCRJ1.10, MCRJ1.11, MCRJ1.12, MCRJ3.5, P2.3, R3.2, R4.2, R9.2, TEST.2, U1.7, U2A.1, U2A.4, U2A.8, U2A.9, U2A.10, U2A.15, U2B.1, U2B.4, U2B.8, U2B.9, U2B.10, U2B.15, U3.1, U4.2, U4.4, U5.1
R6_U3_P2_P6: C3.1, R6.1, U3.2, U3.6
RESET_5V: D1.2, R10.1, U3.3
RESET_5V_OUT: D1.1, MCRJ1.6
RESET_LED: D4.1, R10.2
SERVICE_SW: JAMMA / CHAMMA.R, MCRJ4A.6
TEST_SW: MCRJ4A.7, TEST.1
U1_P6_U1_P2: U1.2, U1.6
U3_CTRL: C2.2, U3.5
U4_BYPASS: C4.1, U4.7
U4_GAIN_P1: C1.1, U4.1
U4_GAIN_P8: C1.2, U4.8
U5_CTRL: C9.1, U5.5
U5_DIS: R7.1, R8.1, U5.7
U5_DIS_R2: P3.1, R7.2
U5_TRIG: C8.1, P3.2, U5.2, U5.6
U6_RCO: U2A.13, U2B.14
V.BATT: D2.1, D3.1, MCRJ1.5
VIDEO_B: JAMMA / CHAMMA.13, MCRJ2.3
VIDEO_G: JAMMA / CHAMMA.N, MCRJ2.2
VIDEO_HSYNC: MCRJ2.4, U1.5
VIDEO_RED: JAMMA / CHAMMA.12, MCRJ2.1
VIDEO_SYNC: JAMMA / CHAMMA.P, R12.2
VIDEO_SYNC_R12: R12.1, U1.3
VIDEO_VSYNC: MCRJ2.5, U1.4
VOL_GND: MCRJ3.3, P1.3
VOL_IN: MCRJ3.1, P1.1
VOL_OUT: MCRJ3.2, P1.2

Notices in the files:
Atari JAMMA Interface.kicad_pcb:
PCB Design Copyright © 2025, Jonathan Zdziarski
All Rights Reserved
Spy Hunter JAMMA Adapter.kicad_pcb:
PCB Design Copyright © 2025, Jonathan Zdziarski. All Rights Reserved.
